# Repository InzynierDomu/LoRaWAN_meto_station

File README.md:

# LoRaWAN meteo station

- [LoRaWAN meto station](#lorawan-meto-station)
  - [About](#about)
  - [Scheme](#scheme)
    - [Part list:](#part-list)
  - [Configuration](#configuration)
  - [IDE](#ide)
  - [Software upload](#software-upload)

## About
End device to measure air temperature, humidity, pressure, and light intense, and send to TTN. More information for this project you will find in this [note](http://www.inzynierdomu.pl/lora-i-lorawan-czesc-3/)

<div align="center">
<h2>Support</h2>

<p>If any of my projects have helped you in your work, studies, or simply made your day better, you can buy me a coffee. </p>
</div>

## Scheme

### Part list:
* U1 Arduino MKR 1300
To board must be connected BME280 and DS18B20. 
## Configuration
Before config this project, prepare an account on TheThingsNetwor. All described [here](http://www.inzynierdomu.pl/lora-i-lorawan-czesc-2/)
Need add device on TTN console to get credentials. Put necessary keys in Config.h file.
To decode information, on TTN use JS formatter ttn_decoder.js.
## IDE
The project is prepared for the Platform IO environment. A video on how to install such an environment can be watched on this [video](https://youtu.be/Em9NuebT2Kc)
## Software upload 
The board may not be programmable during sleep. You should then press the reset button on the board twice quickly. It should appear on a different port and can be programmed.

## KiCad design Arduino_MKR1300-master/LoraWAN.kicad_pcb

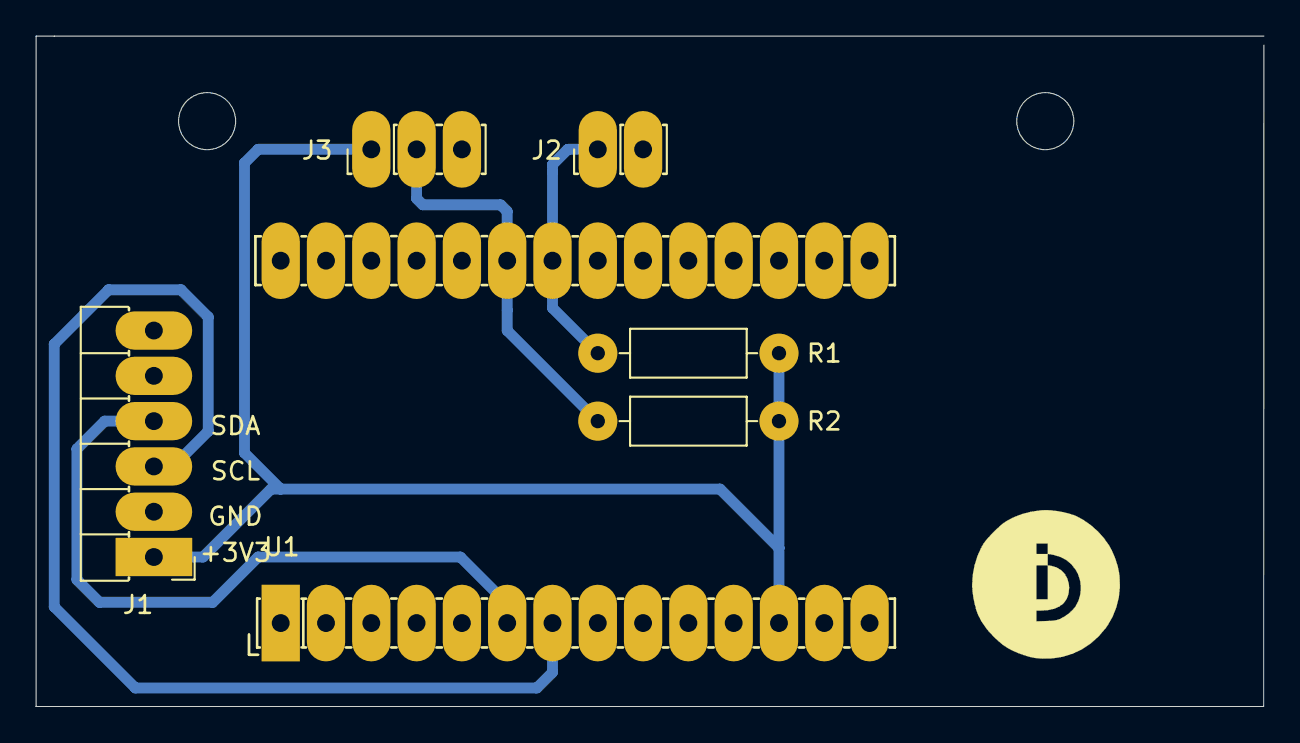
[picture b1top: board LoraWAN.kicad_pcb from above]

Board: 2 copper layers, 68.8 x 37.6 mm, 6 parts (0 on the bottom side), 6 nets.

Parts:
J1: Conn_01x06_Male; PinHeader_1x06_P2.54mm_Horizontal_Oval_NoPinSilk
J2: Conn_01x02_Male; PinHeader_1x02_P2.54mm_Vertical_PAD
J3: Conn_01x03_Male; PinHeader_1x03_P2.54mm_Vertical_PAD
R1, R2: 10k; R_Axial_DIN0207_L6.3mm_D2.5mm_P10.16mm_Horizontal_PAD
U1: Ardiuno_MKR1300; Arduino_MKR1300_Oval

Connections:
GND: J1.2, J2.2, J3.3, U1.11
unnamed: J2.1, R1.2, U1.22
unnamed: J3.2, R2.2, U1.23
SCL: J1.3, U1.7
SDA: J1.4, U1.6
VCC: J1.1, J3.1, R1.1, R2.1, U1.12

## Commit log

2019-11-29 create project
2019-12-04 Move project to platform io
2019-12-04 add sending msg
2019-12-06 cleaning
2019-12-06 add low power libary
2020-05-22 add minor stylistic corrections
2020-09-14 Add schem and PCB
2020-09-14 add Node_RED flow
2022-12-27 add repo new standard files
2022-12-27 clear
2022-12-27 move license
2022-12-27 move doxyfile
2022-12-27 change doxygen path
2022-12-27 add doxygen directory
2022-12-27 fix doxygen path
2022-12-27 add /
2022-12-27 remove / from paths doxygen
2022-12-27 move doxyfile to ./
2022-12-27 ./ to working doxygen path
2022-12-27 refactor measurments
2022-12-27 copy doxyfile for test
2022-12-27 fix naming in lorawan part
2022-12-29 fix build ci
2023-01-01 Add short description about using TTN.
2023-01-01 fix typo in readme
2023-01-01 deploy: 4814e4865997ffb60ff954dd9436fab0cabdb53c
2025-03-07 deploy: d6a50b95d0ff512a3a723dc08d67aaaba06984e7
2025-04-08 deploy: 03a89f32781f8f71ae78f9bd8344557198e1cf61
2025-04-21 add soil moisture measurements
2025-04-21 add get soil moisture
2025-05-08 add new parameter to decoder
2025-05-08 deploy: c3cd40b9616719d7c4222e845d14519ec089ab3d
